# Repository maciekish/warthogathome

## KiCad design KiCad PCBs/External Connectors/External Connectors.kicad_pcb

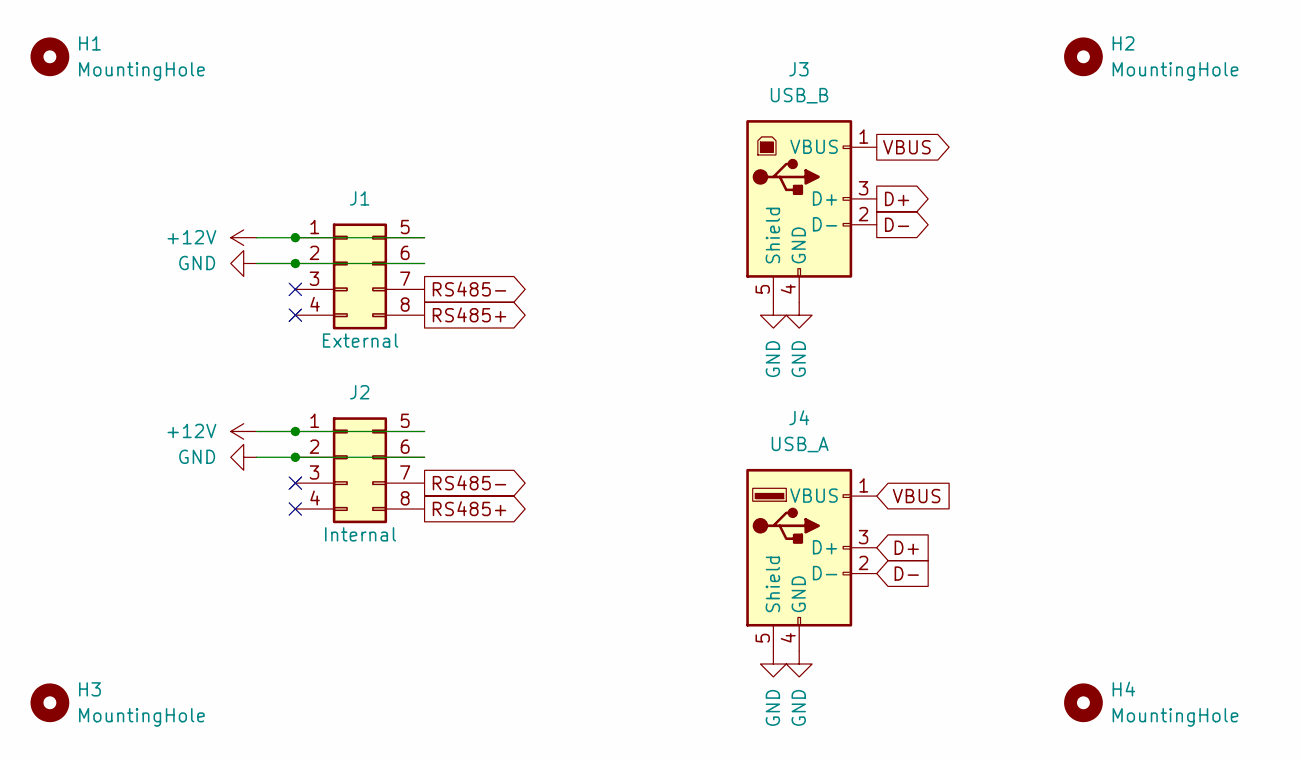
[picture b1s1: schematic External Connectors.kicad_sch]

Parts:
H1, H2, H3, H4: MountingHole; MountingHole_3.2mm_M3
J1, J2: Conn_02x04_Top_Bottom; Molex Micro-Fit 3.0 43045-0800; LCSC C234189
J3: USB_B; USB-B-TH_67068-8000; LCSC C114097
J4: USB_A; USB-A-TH_USB-302-T; LCSC C86461

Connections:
+12V: J1.1, J1.5, J2.1, J2.5
D+: J3.3 (D+), J4.3 (D+)
D-: J3.2 (D-), J4.2 (D-)
GND: J1.2, J1.6, J2.2, J2.6, J3.4 (GND), J3.5 (Shield), J4.4 (GND), J4.5 (Shield)
RS485+: J1.8, J2.8
RS485-: J1.7, J2.7
VBUS: J3.1 (VBUS), J4.1 (VBUS)

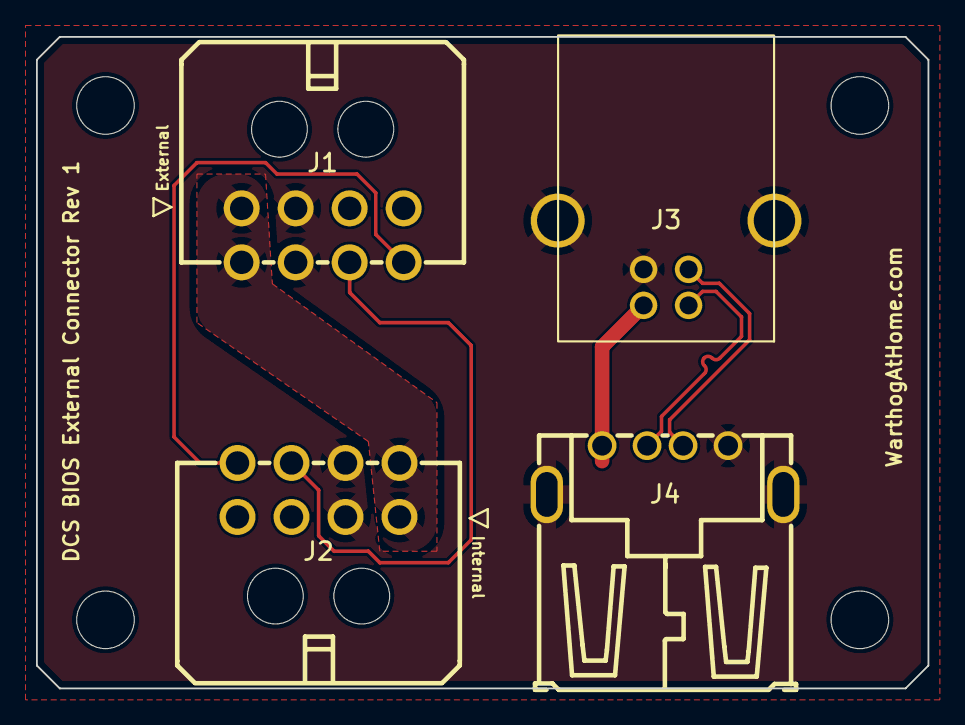
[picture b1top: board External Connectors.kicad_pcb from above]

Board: 2 copper layers, 49.5 x 36.2 mm, 8 parts (0 on the bottom side), 7 nets.

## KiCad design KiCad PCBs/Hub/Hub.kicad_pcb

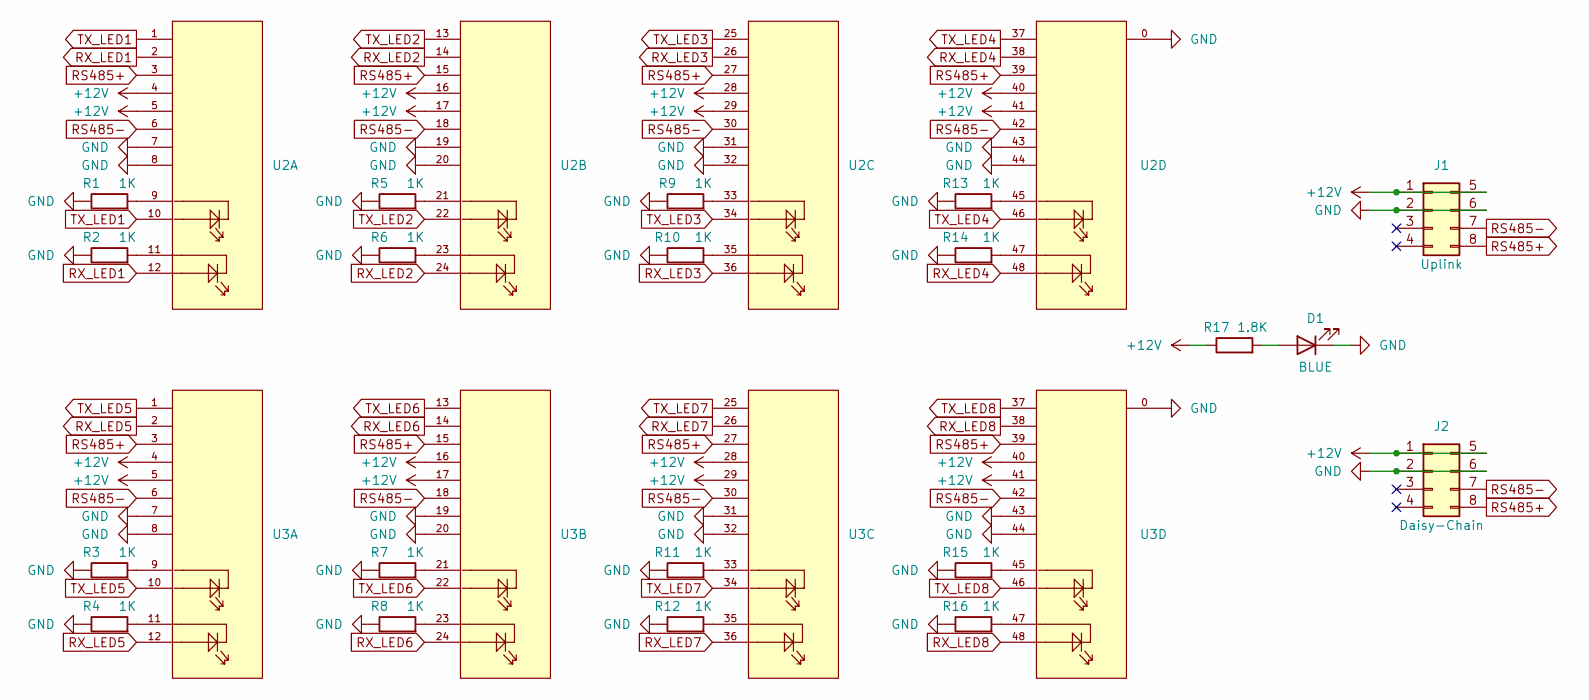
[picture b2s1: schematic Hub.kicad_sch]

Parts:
D1: BLUE; LED_0603_1608Metric; LCSC C72041
J1, J2: Conn_02x04_Top_Bottom; Molex Micro-Fit 3.0 43045-0800; LCSC C234189
R1, R2, R3, R4, R5, R6, R7, R8, R9, R10, R11, R12, R13, R14, R15, R16: 1K; R0805; LCSC C17513
R17: 1.8K; R0805; LCSC C17398
U2, U3: RJ45-B-1*4; RJ45-TH_B-1-4; LCSC C138390

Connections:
+12V: J1.1, J1.5, J2.1, J2.5, R17.1, U2.4, U2.5, U2.16, U2.17, U2.28, U2.29, U2.40, U2.41, U3.4, U3.5, U3.16, U3.17, U3.28, U3.29, U3.40, U3.41
GND: D1.1 (K), J1.2, J1.6, J2.2, J2.6, R1.1, R2.1, R3.1, R4.1, R5.1, R6.1, R7.1, R8.1, R9.1, R10.1, R11.1, R12.1, R13.1, R14.1, R15.1, R16.1, U2.0, U2.7, U2.8, U2.19, U2.20, U2.31, U2.32, U2.43, U2.44, U3.0, U3.7, U3.8, U3.19, U3.20, U3.31, U3.32, U3.43, U3.44
unnamed: D1.2 (A), R17.2
unnamed: R1.2, U2.9
unnamed: R2.2, U2.11
unnamed: R3.2, U3.9
unnamed: R4.2, U3.11
unnamed: R5.2, U2.21
unnamed: R6.2, U2.23
unnamed: R7.2, U3.21
unnamed: R8.2, U3.23
unnamed: R9.2, U2.33
unnamed: R10.2, U2.35
unnamed: R11.2, U3.33
unnamed: R12.2, U3.35
unnamed: R13.2, U2.45
unnamed: R14.2, U2.47
unnamed: R15.2, U3.45
unnamed: R16.2, U3.47
RS485+: J1.8, J2.8, U2.3, U2.15, U2.27, U2.39, U3.3, U3.15, U3.27, U3.39
RS485-: J1.7, J2.7, U2.6, U2.18, U2.30, U2.42, U3.6, U3.18, U3.30, U3.42
RX_LED1: U2.2, U2.12
RX_LED2: U2.14, U2.24
RX_LED3: U2.26, U2.36
RX_LED4: U2.38, U2.48
RX_LED5: U3.2, U3.12
RX_LED6: U3.14, U3.24
RX_LED7: U3.26, U3.36
RX_LED8: U3.38, U3.48
TX_LED1: U2.1, U2.10
TX_LED2: U2.13, U2.22
TX_LED3: U2.25, U2.34
TX_LED4: U2.37, U2.46
TX_LED5: U3.1, U3.10
TX_LED6: U3.13, U3.22
TX_LED7: U3.25, U3.34
TX_LED8: U3.37, U3.46

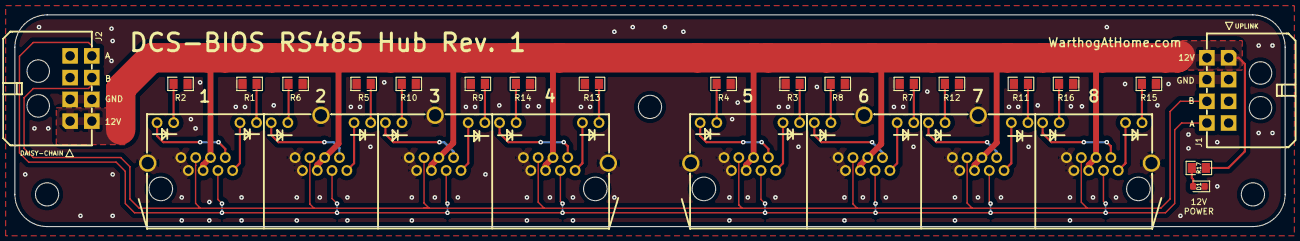
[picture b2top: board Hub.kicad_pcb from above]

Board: 2 copper layers, 175.3 x 29.2 mm, 25 parts (0 on the bottom side), 37 nets.

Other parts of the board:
HOLE-2, HOLE-3, HOLE-4: MountingHole_3.2mm_M3

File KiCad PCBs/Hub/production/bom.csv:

Designator,Footprint,Quantity,Value,LCSC Part #
R7,R0805,1,1K,C17513
R9,R0805,1,1K,C17513
R10,R0805,1,1K,C17513
R6,R0805,1,1K,C17513
R16,R0805,1,1K,C17513
R15,R0805,1,1K,C17513
D1,LED_0603_1608Metric,1,BLUE,C72041
R14,R0805,1,1K,C17513
R4,R0805,1,1K,C17513
R12,R0805,1,1K,C17513
U3,RJ45-TH_B-1-4,1,RJ45-B-1*4,C138390
R17,R0805,1,1.8K,
R8,R0805,1,1K,C17513
R5,R0805,1,1K,C17513
R11,R0805,1,1K,C17513
R2,R0805,1,1K,C17513
U2,RJ45-TH_B-1-4,1,RJ45-B-1*4,C138390
R1,R0805,1,1K,C17513
R13,R0805,1,1K,C17513
R3,R0805,1,1K,C17513

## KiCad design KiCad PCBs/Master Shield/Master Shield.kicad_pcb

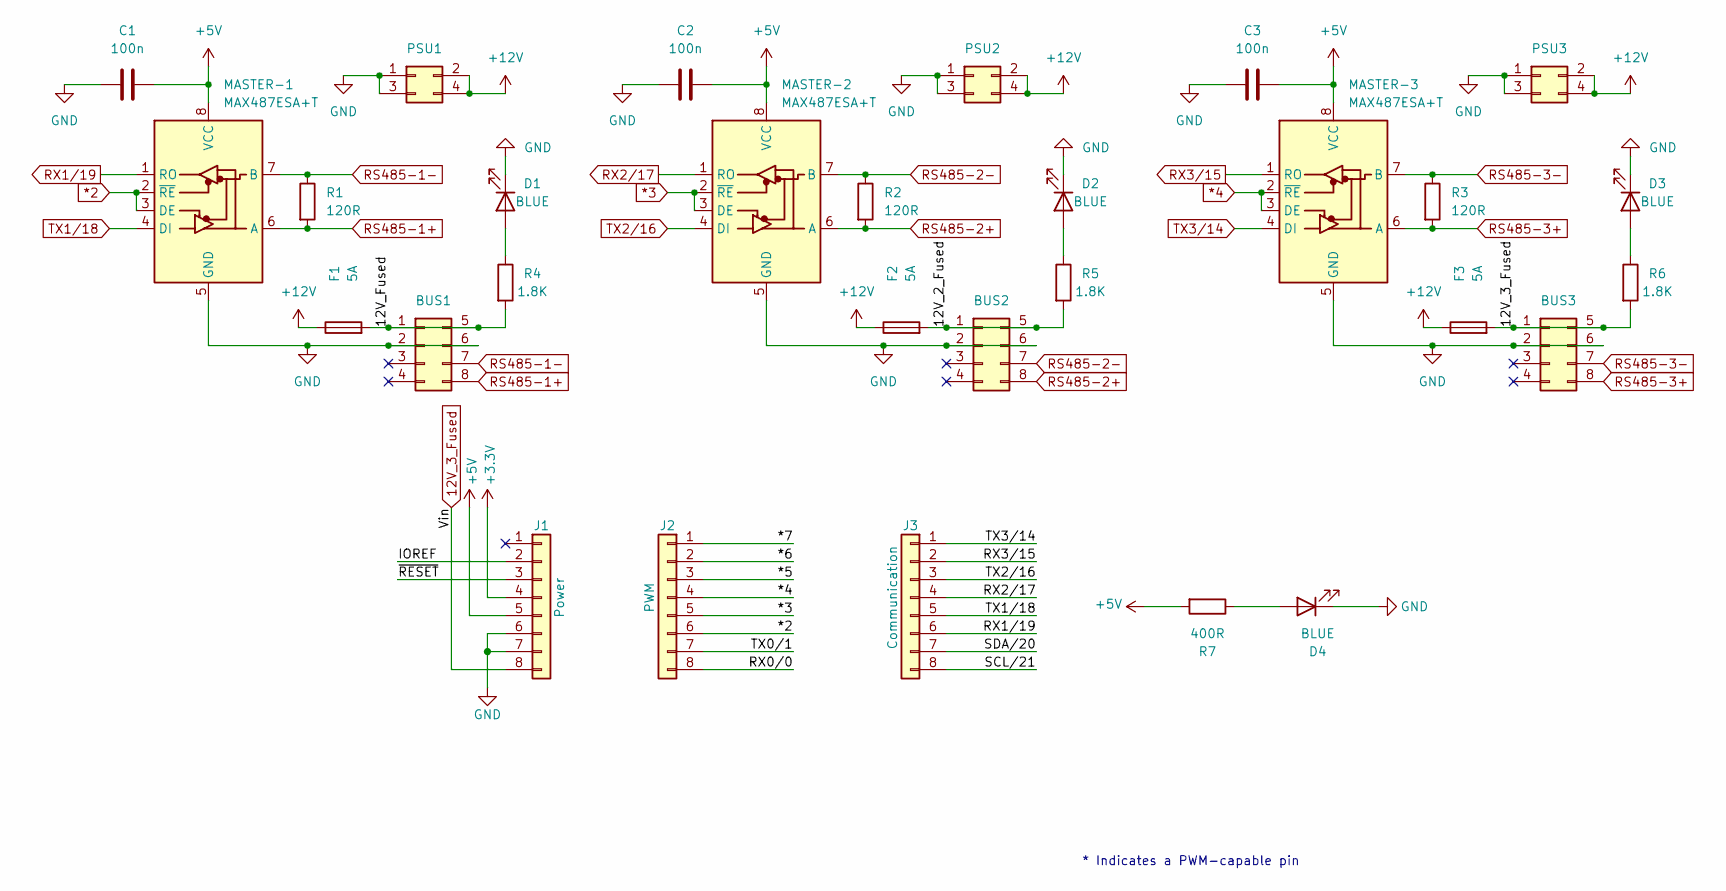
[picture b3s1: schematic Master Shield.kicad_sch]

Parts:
BUS1, BUS2, BUS3: Conn_02x04_Top_Bottom; CONN-TH_430450812; LCSC C277661
C1, C2, C3: 100n; C0402; LCSC C1525
D1, D2, D3, D4: BLUE; LED_0603_1608Metric; LCSC C72041
F1, F2, F3: 5A; FUSE_BK-6013
J1: Power; PinHeader_1x08_P2.54mm_Vertical; LCSC C124381
J2: PWM; PinHeader_1x08_P2.54mm_Vertical; LCSC C124381
J3: Communication; PinHeader_1x08_P2.54mm_Vertical; LCSC C124381
MASTER-1, MASTER-2, MASTER-3: MAX487ESA+T; SOIC-8_L5.0-W4.0-P1.27-LS6.0-BL; LCSC C9953
PSU1, PSU2, PSU3: Conn_02x02_Top_Bottom; CONN-TH_0430450400
R1, R2, R3: 120R; R_0805_2012Metric; LCSC C17437
R4, R5, R6: 1.8K; R_0805_2012Metric; LCSC C17398
R7: 400R; R_0805_2012Metric; LCSC C17655

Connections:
12V_3_Fused: BUS3.1, BUS3.5, F3.2, J1.8, R6.2
*2: J2.6, MASTER-1.2 (~RE), MASTER-1.3 (DE)
*3: J2.5, MASTER-2.2 (~RE), MASTER-2.3 (DE)
*4: J2.4, MASTER-3.2 (~RE), MASTER-3.3 (DE)
+3V3: J1.4
+5V: C1.2, C2.2, C3.2, J1.5, MASTER-1.8 (VCC), MASTER-2.8 (VCC), MASTER-3.8 (VCC), R7.2
/12V_2_Fused: BUS2.1, BUS2.5, F2.2, R5.2
/12V_Fused: BUS1.1, BUS1.5, F1.2, R4.2
/*5: J2.3
/*6: J2.2
/*7: J2.1
/IOREF: J1.2
/RX0/0: J2.8
/SCL/21: J3.8
/SDA/20: J3.7
/TX0/1: J2.7
/~RESET: J1.3
GND: BUS1.2, BUS1.6, BUS2.2, BUS2.6, BUS3.2, BUS3.6, C1.1, C2.1, C3.1, D1.1 (K), D2.1 (K), D3.1 (K), D4.1 (K), J1.6, J1.7, MASTER-1.5 (GND), MASTER-2.5 (GND), MASTER-3.5 (GND), PSU1.1, PSU1.3, PSU2.1, PSU2.3, PSU3.1, PSU3.3
unnamed: D1.2 (A), R4.1
unnamed: D2.2 (A), R5.1
unnamed: D3.2 (A), R6.1
unnamed: D4.2 (A), R7.1
RS485-1+: BUS1.8, MASTER-1.6 (A), R1.2
RS485-1-: BUS1.7, MASTER-1.7 (B), R1.1
RS485-2+: BUS2.8, MASTER-2.6 (A), R2.2
RS485-2-: BUS2.7, MASTER-2.7 (B), R2.1
RS485-3+: BUS3.8, MASTER-3.6 (A), R3.2
RS485-3-: BUS3.7, MASTER-3.7 (B), R3.1
RX1/19: J3.6, MASTER-1.1 (RO)
RX2/17: J3.4, MASTER-2.1 (RO)
RX3/15: J3.2, MASTER-3.1 (RO)
TX1/18: J3.5, MASTER-1.4 (DI)
TX2/16: J3.3, MASTER-2.4 (DI)
TX3/14: J3.1, MASTER-3.4 (DI)

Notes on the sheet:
* Indicates a PWM-capable pin

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
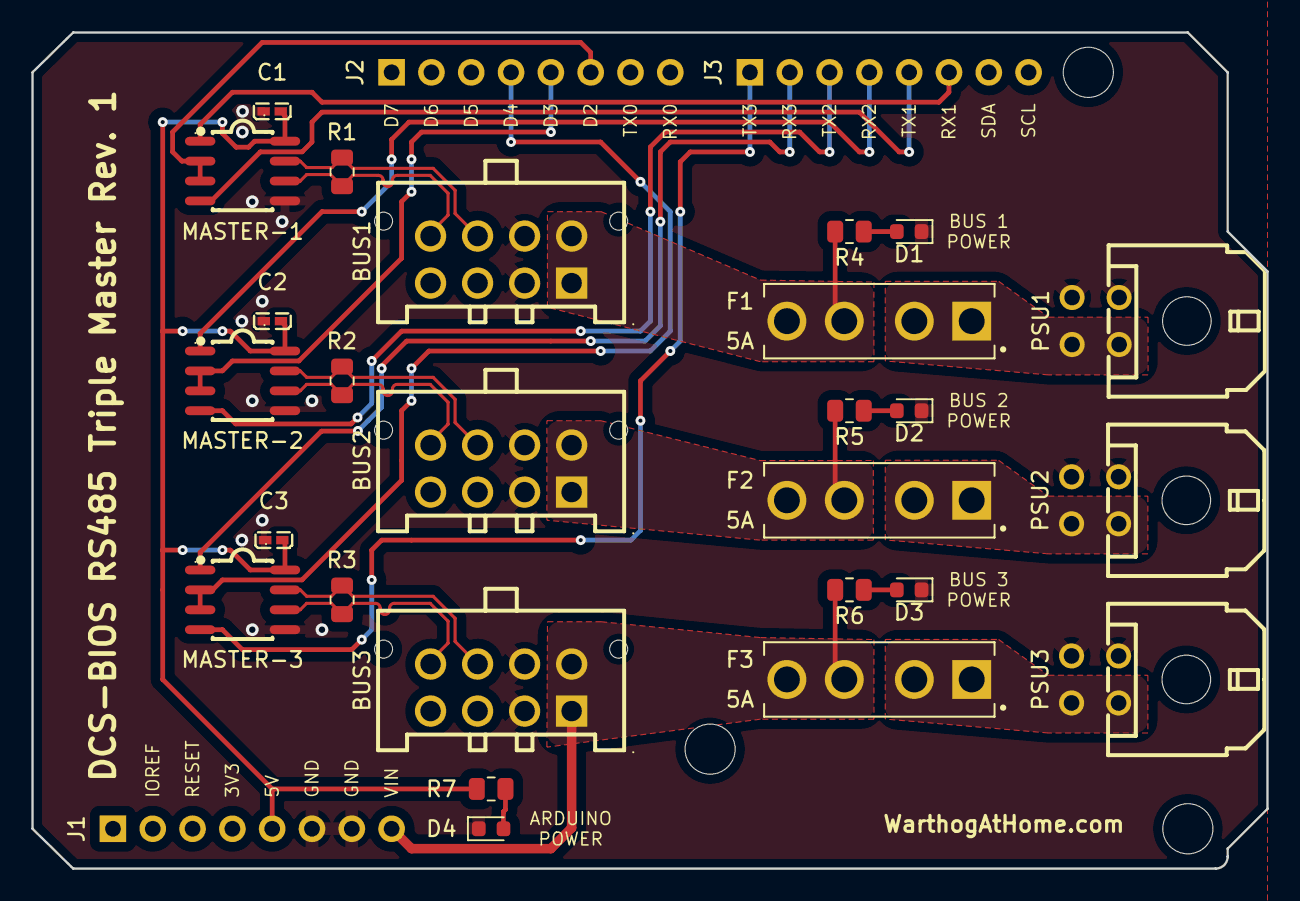
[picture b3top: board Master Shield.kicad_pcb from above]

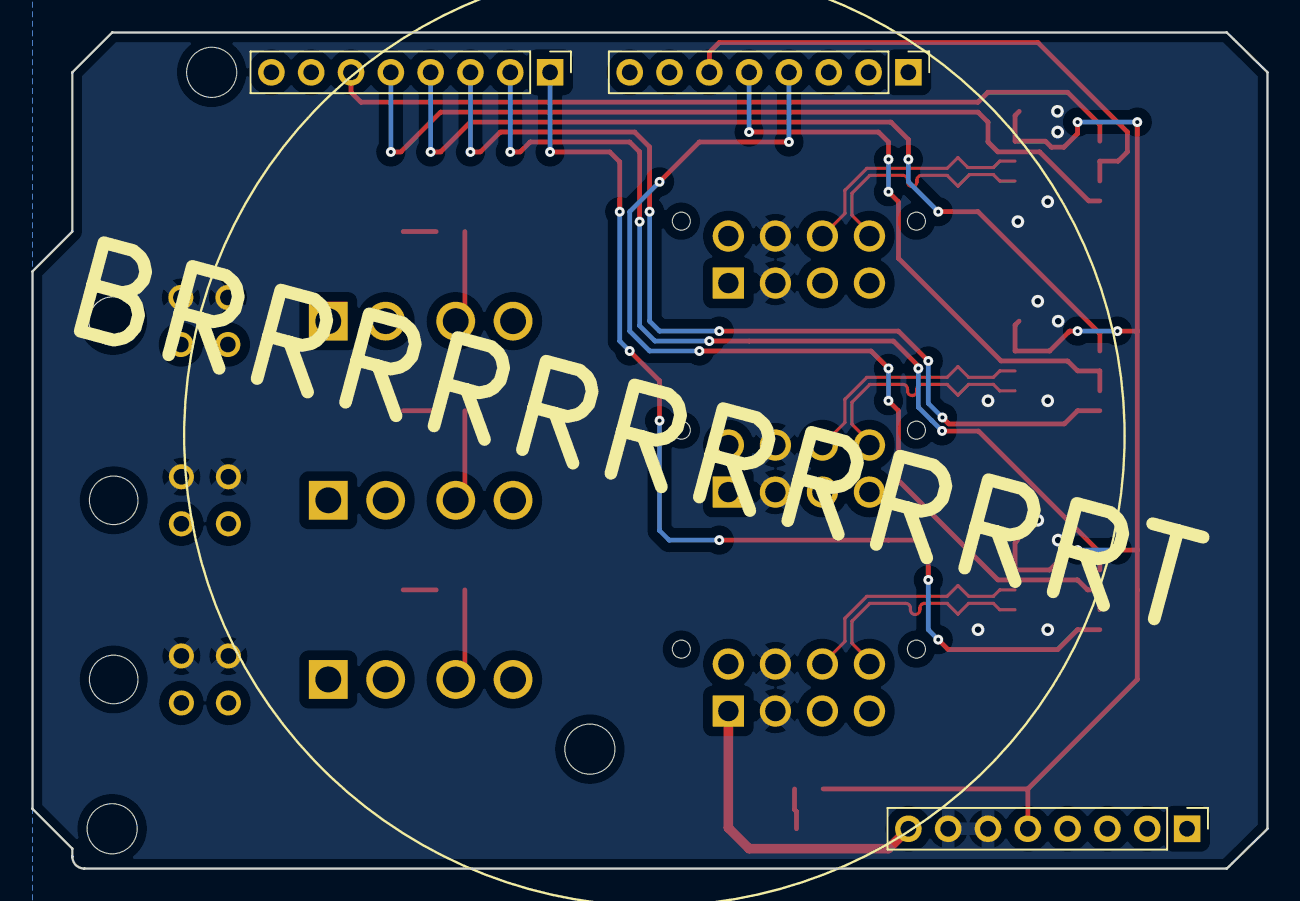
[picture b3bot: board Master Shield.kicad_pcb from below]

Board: 2 copper layers, 78.8 x 53.3 mm, 32 parts (3 on the bottom side), 27 nets.

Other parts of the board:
MH4, MH5, MH6: MountingHole_3.2mm

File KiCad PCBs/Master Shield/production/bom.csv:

Designator,Footprint,Quantity,Value,LCSC Part #
R2,R_0805_2012Metric,1,120R,C17437
MASTER-2,SOIC-8_L5.0-W4.0-P1.27-LS6.0-BL,1,MAX487ESA+T,C9953
R4,R_0805_2012Metric,1,1.8K,C17398
D3,LED_0603_1608Metric,1,BLUE,C72041
BUS3,CONN-TH_430450812,1,Conn_02x04_Top_Bottom,C277661
C1,C0402,1,100n,C1525
C3,C0402,1,100n,C1525
R5,R_0805_2012Metric,1,1.8K,C17398
MASTER-1,SOIC-8_L5.0-W4.0-P1.27-LS6.0-BL,1,MAX487ESA+T,C9953
D1,LED_0603_1608Metric,1,BLUE,C72041
D2,LED_0603_1608Metric,1,BLUE,C72041
D4,LED_0603_1608Metric,1,BLUE,C72041
C2,C0402,1,100n,C1525
R6,R_0805_2012Metric,1,1.8K,C17398
R7,R_0805_2012Metric,1,400R,C17655
BUS2,CONN-TH_430450812,1,Conn_02x04_Top_Bottom,C277661
MASTER-3,SOIC-8_L5.0-W4.0-P1.27-LS6.0-BL,1,MAX487ESA+T,C9953
R1,R_0805_2012Metric,1,120R,C17437
R3,R_0805_2012Metric,1,120R,C17437
BUS1,CONN-TH_430450812,1,Conn_02x04_Top_Bottom,C277661
J1,PinHeader_1x08_P2.54mm_Vertical,1,Power,C124381
J2,PinHeader_1x08_P2.54mm_Vertical,1,PWM,C124381
J3,PinHeader_1x08_P2.54mm_Vertical,1,Communication,C124381

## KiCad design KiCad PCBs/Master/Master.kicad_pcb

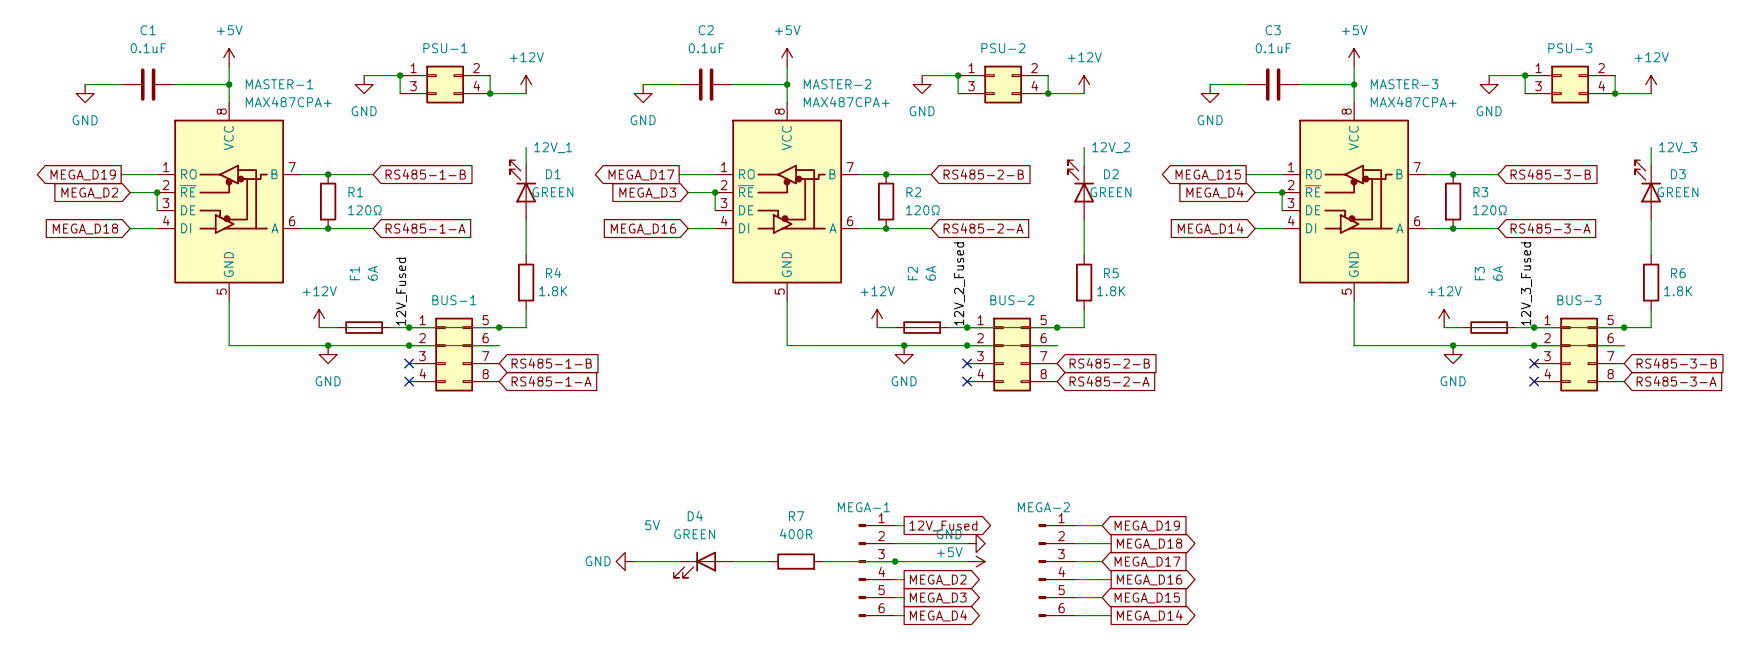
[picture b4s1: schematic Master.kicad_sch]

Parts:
BUS-1, BUS-2, BUS-3: Conn_02x04_Top_Bottom; Molex 43045-0800
C1, C2, C3: 0.1uF; FA14
D1, D2, D3, D4: GREEN; LED_1210_3225Metric_Pad1.42x2.65mm_HandSolder
F1, F2, F3: 6A; FUSE_BK-6013
MASTER-1, MASTER-2, MASTER-3: MAX487CPA+; DIP-8_W7.62mm_LongPads
MEGA-1, MEGA-2: Conn_01x06_Male; SHDR6W64P0X250_1X6_1740X575X700P
PSU-1, PSU-2, PSU-3: Conn_02x02_Top_Bottom; Molex 43045-0400
R1, R2, R3: 120Ω; R_Axial_DIN0207_L6.3mm_D2.5mm_P7.62mm_Horizontal
R4, R5, R6: 1.8K; R_1210_3225Metric_Pad1.30x2.65mm_HandSolder
R7: 400R; R_1210_3225Metric_Pad1.30x2.65mm_HandSolder

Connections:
12V_Fused: BUS-1.1, BUS-1.5, F1.2, MEGA-1.1, R4.2
+5V: C1.2, C2.2, C3.2, MASTER-1.8 (VCC), MASTER-2.8 (VCC), MASTER-3.8 (VCC), MEGA-1.3, R7.2
/12V_2_Fused: BUS-2.1, BUS-2.5, F2.2, R5.2
/12V_3_Fused: BUS-3.1, BUS-3.5, F3.2, R6.2
GND: BUS-1.2, BUS-1.6, BUS-2.2, BUS-2.6, BUS-3.2, BUS-3.6, C1.1, C2.1, C3.1, D4.1 (K), MASTER-1.5 (GND), MASTER-2.5 (GND), MASTER-3.5 (GND), MEGA-1.2, PSU-1.1, PSU-1.3, PSU-2.1, PSU-2.3, PSU-3.1, PSU-3.3
MEGA_D2: MASTER-1.2 (~RE), MASTER-1.3 (DE), MEGA-1.4
MEGA_D3: MASTER-2.2 (~RE), MASTER-2.3 (DE), MEGA-1.5
MEGA_D4: MASTER-3.2 (~RE), MASTER-3.3 (DE), MEGA-1.6
MEGA_D14: MASTER-3.4 (DI), MEGA-2.6
MEGA_D15: MASTER-3.1 (RO), MEGA-2.5
MEGA_D16: MASTER-2.4 (DI), MEGA-2.4
MEGA_D17: MASTER-2.1 (RO), MEGA-2.3
MEGA_D18: MASTER-1.4 (DI), MEGA-2.2
MEGA_D19: MASTER-1.1 (RO), MEGA-2.1
unnamed: D1.2 (A), R4.1
unnamed: D2.2 (A), R5.1
unnamed: D3.2 (A), R6.1
unnamed: D4.2 (A), R7.1
RS485-1-A: BUS-1.8, MASTER-1.6 (A), R1.2
RS485-1-B: BUS-1.7, MASTER-1.7 (B), R1.1
RS485-2-A: BUS-2.8, MASTER-2.6 (A), R2.2
RS485-2-B: BUS-2.7, MASTER-2.7 (B), R2.1
RS485-3-A: BUS-3.8, MASTER-3.6 (A), R3.2
RS485-3-B: BUS-3.7, MASTER-3.7 (B), R3.1

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
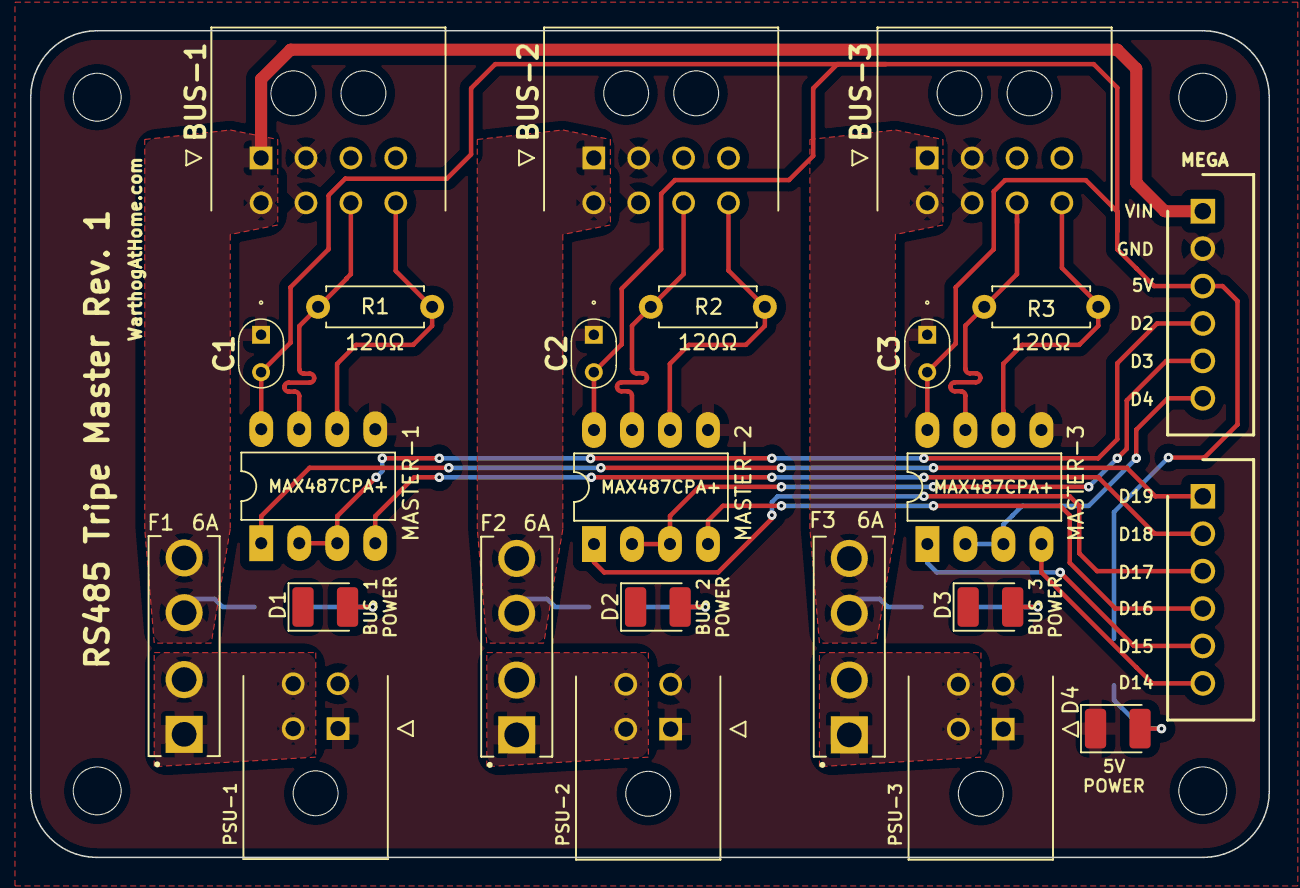
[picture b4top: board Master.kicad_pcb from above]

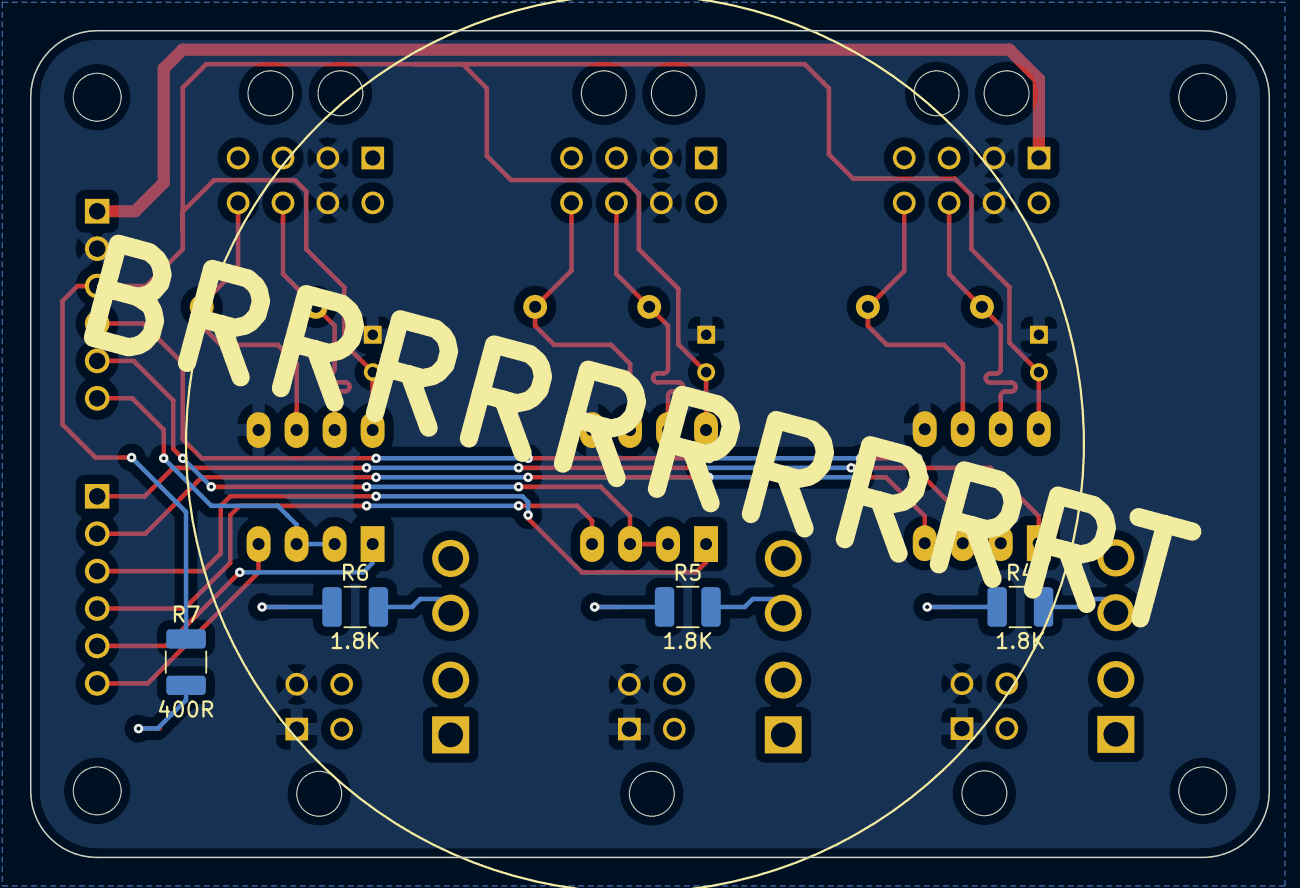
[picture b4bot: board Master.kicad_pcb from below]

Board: 2 copper layers, 82.8 x 55.2 mm, 32 parts (4 on the bottom side), 27 nets.

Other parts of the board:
HOLE-1, HOLE-2, HOLE-3, HOLE-4: MountingHole_3.2mm_M3

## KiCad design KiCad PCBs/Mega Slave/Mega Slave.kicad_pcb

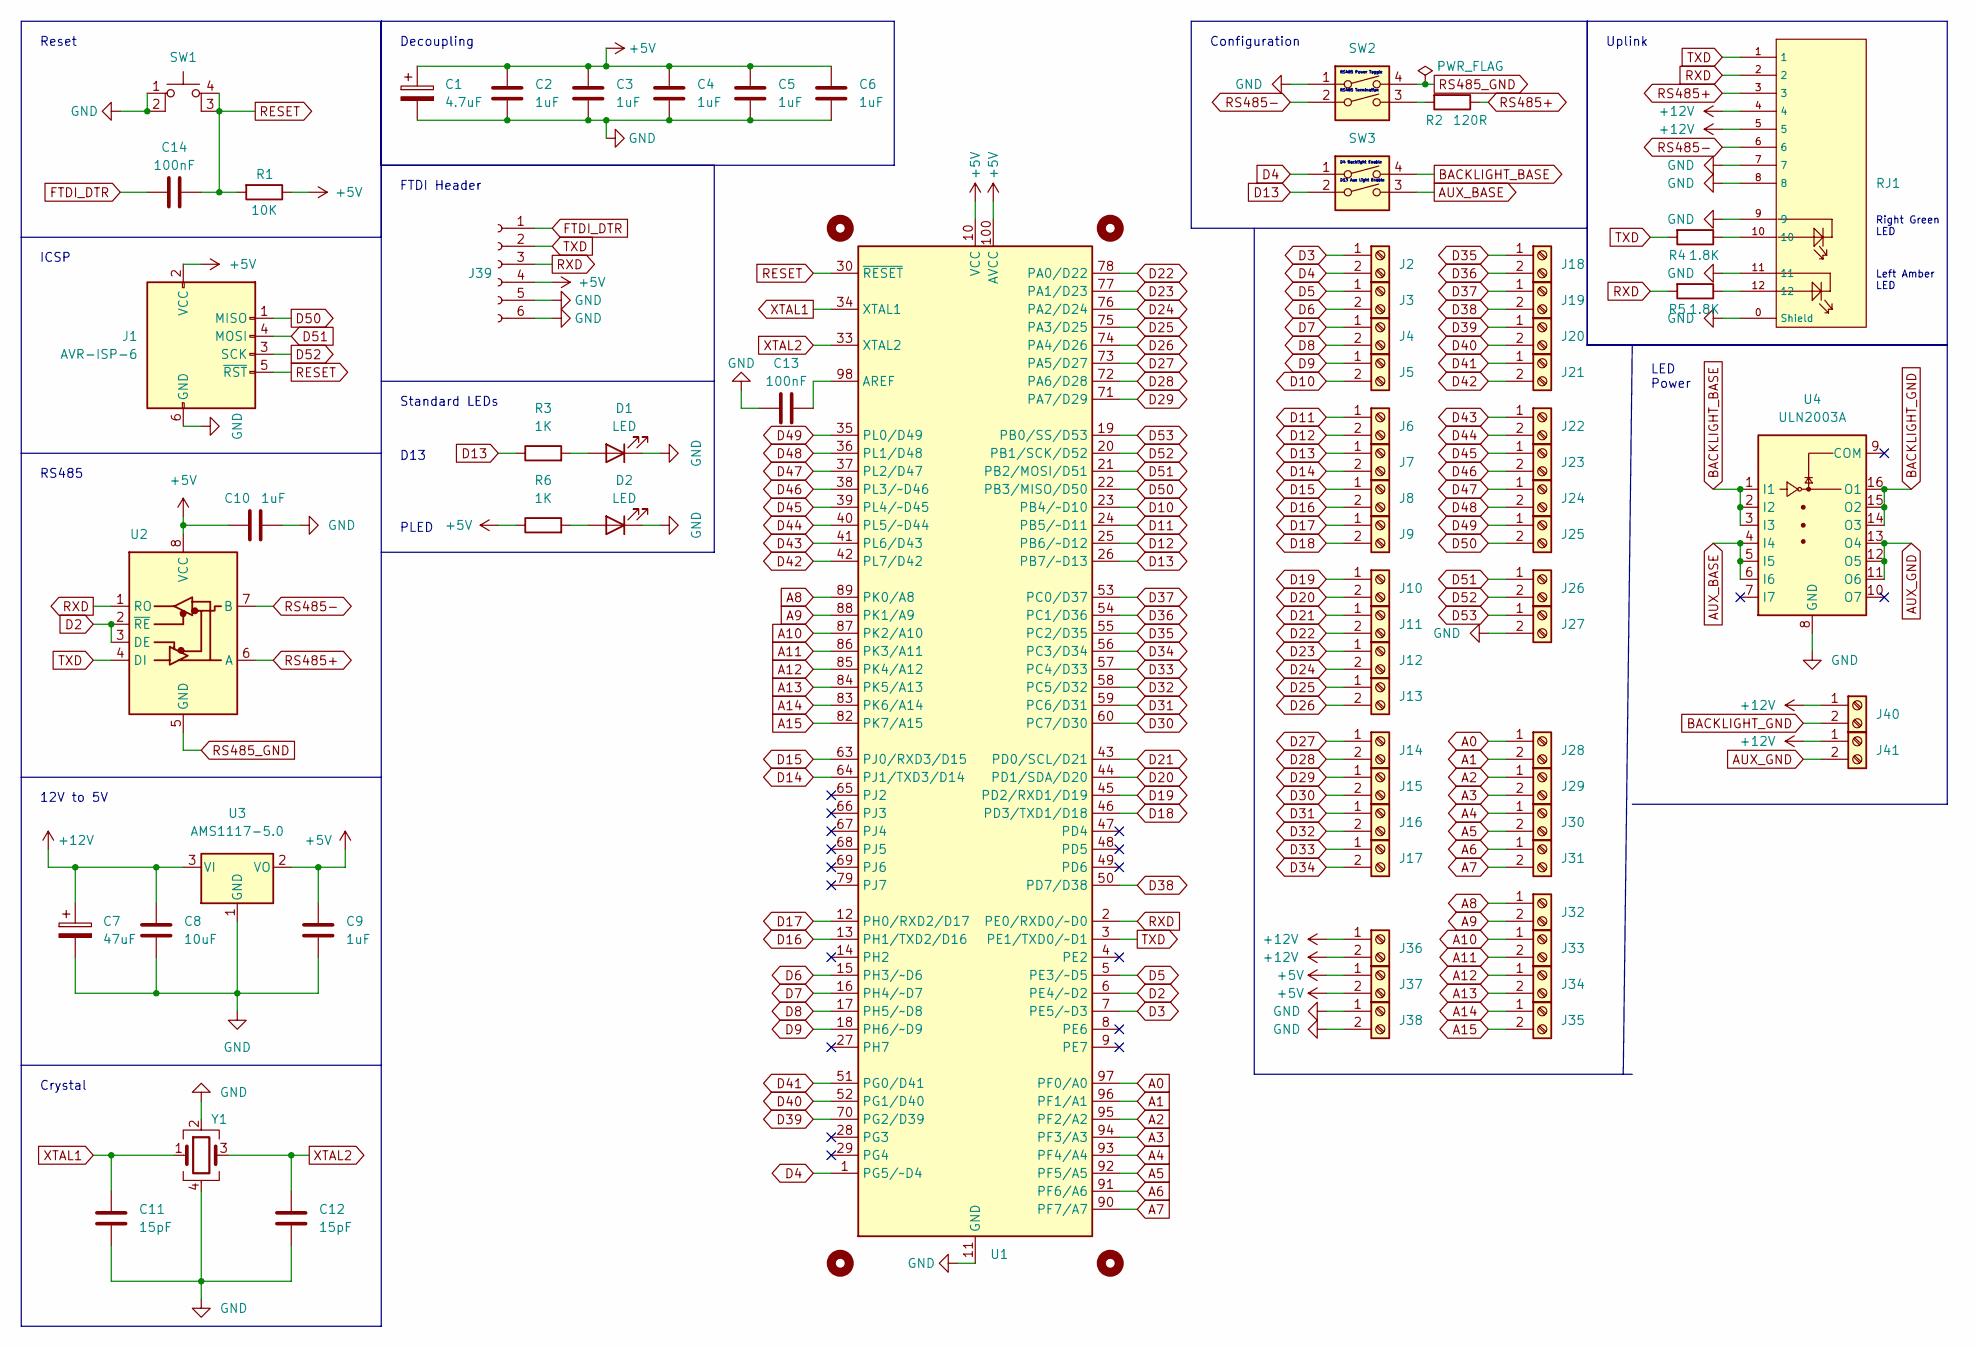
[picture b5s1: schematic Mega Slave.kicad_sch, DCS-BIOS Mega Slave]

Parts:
C1: 4.7uF; C0805; LCSC C1779
C2, C3, C4, C5, C6, C9, C10: 1uF; C0402; LCSC C52923
C7: 47uF; CP_Elec_5x5.4; LCSC C96178
C8: 10uF; C0402; LCSC C15525
C11, C12: 15pF; C0402; LCSC C1548
C13, C14: 100nF; C0402; LCSC C1525
D1, D2: LED; LED_0603_1608Metric; LCSC C72041
H1, H2, H3, H4: MountingHole; MountingHole_3.2mm_M3
J1: AVR-ISP-6; PinHeader_2x03_P2.54mm_Vertical; LCSC C492420
J2, J3, J4, J5, J6, J7, J8, J9, J10, J11, J12, J13, J14, J15, J16, J17, J18, J19, J20, J21, J22, J23, J24, J25, J26, J27, J28, J29, J30, J31, J32, J33, J34, J35, J36, J37, J38, J40, J41: Screw_Terminal_01x02; CONN-TH_XY308-2.54-2P; LCSC C557685
J39: Conn_01x06_Female; PinSocket_1x06_P2.54mm_Vertical; LCSC C40877
R1: 10K; R_0805_2012Metric; LCSC C17414
R2: 120R; R_0805_2012Metric; LCSC C17437
R3, R6: 1K; R_0805_2012Metric; LCSC C17513
R4, R5: 1.8K; R_0805_2012Metric; LCSC C17398
RJ1: RJ45-B-1*1; RJ45-TH_B-1-1; LCSC C138392
SW1: SW_MEC_5E; SW-SMD_4P-L5.1-W5.1-P3.70-LS6.5-TL-2; LCSC C318884
SW2, SW3: SW_DIP_x02; SW-SMD_DSHP02TSGER; LCSC C367376
U1: ATmega2560-16A; TQFP-100_14x14mm_P0.5mm; LCSC C22460
U2: MAX487ESA+T; SOIC-8_L5.0-W4.0-P1.27-LS6.0-BL; LCSC C9953
U3: AMS1117-5.0; SOT-223-3_TabPin2; LCSC C6187
U4: ULN2003A; SOP-16_L10.0-W3.9-P1.27-LS6.0-BL; LCSC C7512
Y1: Crystal_GND24; Crystal_SMD_3225-4Pin_3.2x2.5mm; LCSC C13738

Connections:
+5V: C1.1, C2.1, C3.1, C4.1, C5.1, C6.1, C9.1, C10.1, J1.2 (VCC), J37.1, J37.2, J39.4, R1.1, R6.1, U1.10 (VCC), U1.31 (VCC), U1.61 (VCC), U1.80 (VCC), U1.100 (AVCC), U2.8 (VCC), U3.2 (VO)
+12V: C7.1, C8.1, J36.1, J36.2, J40.1, J41.1, RJ1.4, RJ1.5, U3.3 (VI)
A0: J28.1, U1.97 (PF0/A0)
A1: J28.2, U1.96 (PF1/A1)
A2: J29.1, U1.95 (PF2/A2)
A3: J29.2, U1.94 (PF3/A3)
A4: J30.1, U1.93 (PF4/A4)
A5: J30.2, U1.92 (PF5/A5)
A6: J31.1, U1.91 (PF6/A6)
A7: J31.2, U1.90 (PF7/A7)
A8: J32.1, U1.89 (PK0/A8)
A9: J32.2, U1.88 (PK1/A9)
A10: J33.1, U1.87 (PK2/A10)
A11: J33.2, U1.86 (PK3/A11)
A12: J34.1, U1.85 (PK4/A12)
A13: J34.2, U1.84 (PK5/A13)
A14: J35.1, U1.83 (PK6/A14)
A15: J35.2, U1.82 (PK7/A15)
AUX_BASE: SW3.3, U4.4 (I4), U4.5 (I5), U4.6 (I6)
AUX_GND: J41.2, U4.11 (O6), U4.12 (O5), U4.13 (O4)
BACKLIGHT_BASE: SW3.4, U4.1 (I1), U4.2 (I2), U4.3 (I3)
BACKLIGHT_GND: J40.2, U4.14 (O3), U4.15 (O2), U4.16 (O1)
D2: U1.6 (PE4/~D2), U2.2 (~RE), U2.3 (DE)
D3: J2.1, U1.7 (PE5/~D3)
D4: J2.2, SW3.1, U1.1 (PG5/~D4)
D5: J3.1, U1.5 (PE3/~D5)
D6: J3.2, U1.15 (PH3/~D6)
D7: J4.1, U1.16 (PH4/~D7)
D8: J4.2, U1.17 (PH5/~D8)
D9: J5.1, U1.18 (PH6/~D9)
D10: J5.2, U1.23 (PB4/~D10)
D11: J6.1, U1.24 (PB5/~D11)
D12: J6.2, U1.25 (PB6/~D12)
D13: J7.1, R3.1, SW3.2, U1.26 (PB7/~D13)
D14: J7.2, U1.64 (PJ1/TXD3/D14)
D15: J8.1, U1.63 (PJ0/RXD3/D15)
D16: J8.2, U1.13 (PH1/TXD2/D16)
D17: J9.1, U1.12 (PH0/RXD2/D17)
D18: J9.2, U1.46 (PD3/TXD1/D18)
D19: J10.1, U1.45 (PD2/RXD1/D19)
D20: J10.2, U1.44 (PD1/SDA/D20)
D21: J11.1, U1.43 (PD0/SCL/D21)
D22: J11.2, U1.78 (PA0/D22)
D23: J12.1, U1.77 (PA1/D23)
D24: J12.2, U1.76 (PA2/D24)
D25: J13.1, U1.75 (PA3/D25)
D26: J13.2, U1.74 (PA4/D26)
D27: J14.1, U1.73 (PA5/D27)
D28: J14.2, U1.72 (PA6/D28)
D29: J15.1, U1.71 (PA7/D29)
D30: J15.2, U1.60 (PC7/D30)
D31: J16.1, U1.59 (PC6/D31)
D32: J16.2, U1.58 (PC5/D32)
D33: J17.1, U1.57 (PC4/D33)
D34: J17.2, U1.56 (PC3/D34)
D35: J18.1, U1.55 (PC2/D35)
D36: J18.2, U1.54 (PC1/D36)
D37: J19.1, U1.53 (PC0/D37)
D38: J19.2, U1.50 (PD7/D38)
D39: J20.1, U1.70 (PG2/D39)
D40: J20.2, U1.52 (PG1/D40)
D41: J21.1, U1.51 (PG0/D41)
D42: J21.2, U1.42 (PL7/D42)
D43: J22.1, U1.41 (PL6/D43)
D44: J22.2, U1.40 (PL5/~D44)
D45: J23.1, U1.39 (PL4/~D45)
D46: J23.2, U1.38 (PL3/~D46)
D47: J24.1, U1.37 (PL2/D47)
D48: J24.2, U1.36 (PL1/D48)
D49: J25.1, U1.35 (PL0/D49)
D50: J1.1 (MISO), J25.2, U1.22 (PB3/MISO/D50)
D51: J1.4 (MOSI), J26.1, U1.21 (PB2/MOSI/D51)
D52: J1.3 (SCK), J26.2, U1.20 (PB1/SCK/D52)
D53: J27.1, U1.19 (PB0/SS/D53)
FTDI_DTR: C14.2, J39.1
GND: C1.2, C2.2, C3.2, C4.2, C5.2, C6.2, C7.2, C8.2, C9.2, C10.2, C11.1, C12.2, C13.1, D1.1 (K), D2.1 (K), J1.6 (GND), J27.2, J38.1, J38.2, J39.5, J39.6, RJ1.0 (Shield), RJ1.7, RJ1.8, RJ1.9, RJ1.11, SW1.1, SW1.2, SW2.1, U1.11 (GND), U1.32 (GND), U1.62 (GND), U1.81 (GND), U1.99 (GND), U3.1 (GND), U4.8 (GND), Y1.2, Y1.4
unnamed: C13.2, U1.98 (AREF)
unnamed: D1.2 (A), R3.2
unnamed: D2.2 (A), R6.2
unnamed: R2.2, SW2.3
unnamed: R4.1, RJ1.10
unnamed: R5.1, RJ1.12
RESET: C14.1, J1.5 (~RST), R1.2, SW1.3 (K), SW1.4 (A), U1.30 (~RESET)
RS485+: R2.1, RJ1.3, U2.6 (A)
RS485-: RJ1.6, SW2.2, U2.7 (B)
RS485_GND: SW2.4, U2.5 (GND)
RXD: J39.3, R5.2, RJ1.2, U1.2 (PE0/RXD0/~D0), U2.1 (RO)
TXD: J39.2, R4.2, RJ1.1, U1.3 (PE1/TXD0/~D1), U2.4 (DI)
XTAL1: C11.2, U1.34 (XTAL1), Y1.1
XTAL2: C12.1, U1.33 (XTAL2), Y1.3

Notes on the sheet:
RS485
Reset
LED Power
Right Green LED
Configuration
Crystal
Standard LEDs
Decoupling
Left Amber LED
RS485 Termination
D4 Backlight Enable
12V to 5V
RS485 Power Toggle
Uplink
D13 Aux Light Enable
D13
FTDI Header
ICSP
PLED

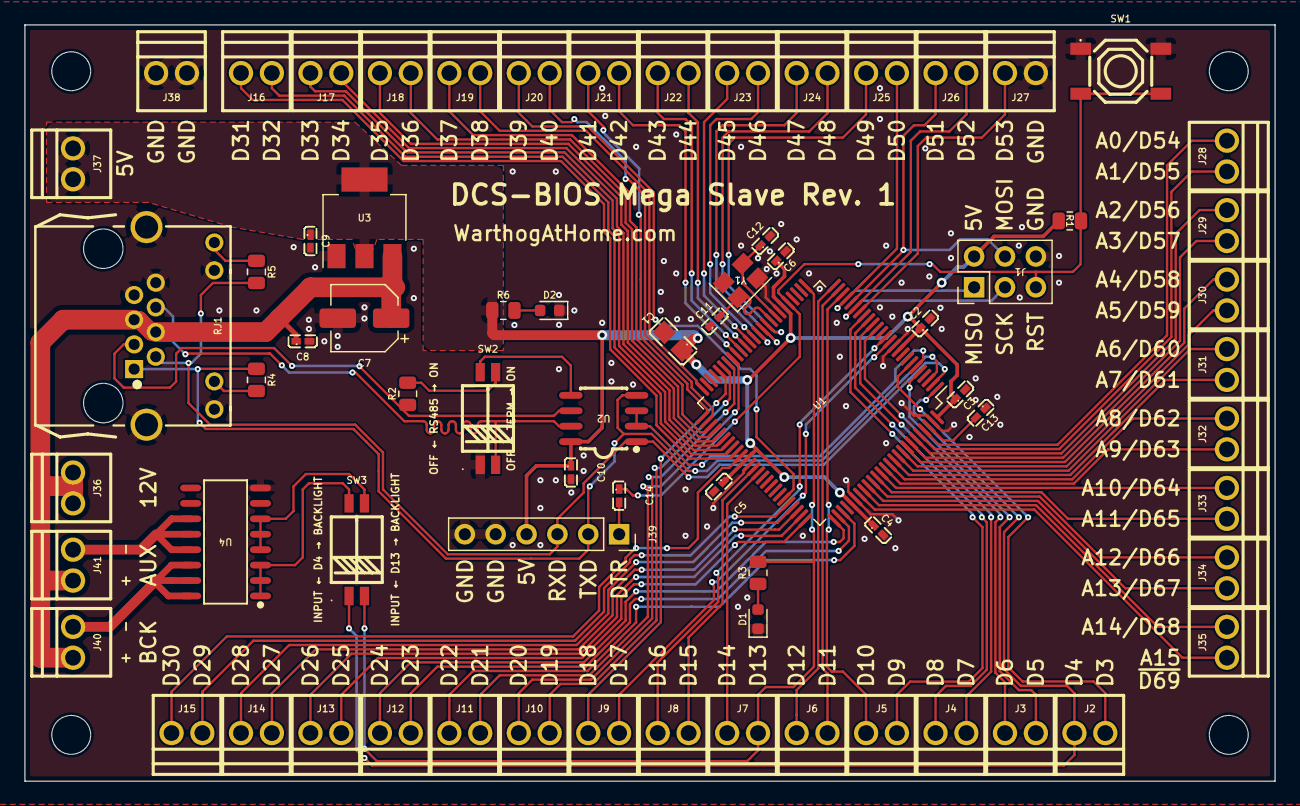
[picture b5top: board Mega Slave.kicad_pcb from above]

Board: 2 copper layers, 102.9 x 62.2 mm, 76 parts (0 on the bottom side), 90 nets.
